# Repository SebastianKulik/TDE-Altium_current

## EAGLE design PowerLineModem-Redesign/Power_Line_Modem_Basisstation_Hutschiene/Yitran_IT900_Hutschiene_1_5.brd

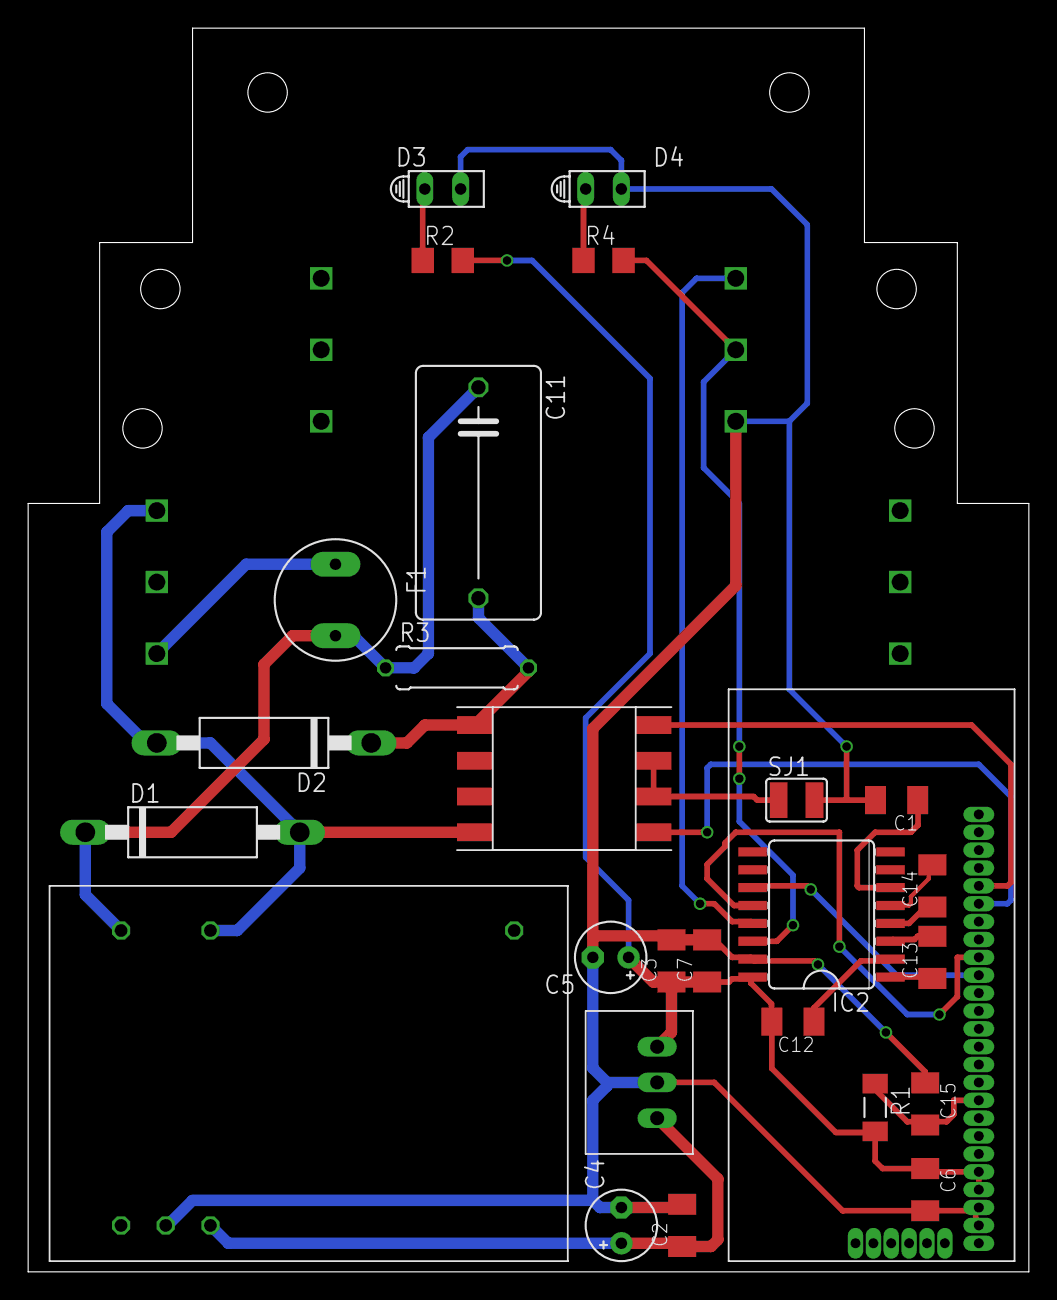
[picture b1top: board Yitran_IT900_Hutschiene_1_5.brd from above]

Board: 2 copper layers, 71.1 x 88.4 mm, 28 parts (0 on the bottom side), 23 nets.

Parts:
C1, C2, C3, C6, C7, C12, C13, C14, C15: 100n; C1206K
C4, C5: 4µ7; E2,5-5
C11: 470n; C150-091X182
D1: P6KE418C; CB417-15
D2: P6KE6V8C; CB417-15
D3: Power_3,3V rot; HLMP6
D4: TxD gruen; HLMP6
F1: 1A; TR5
IC2: MAX3232CWE; SO16L
R1: 100k; M1406
R2, R4: 330R; R1206
R3: 470k; 0309/10
SJ1: SJW
U$1: RECOM_783_3; RECOM785X
U$2: LDG-A-12
U$3: MODEMSTECKER; MODEM_FUSS
U$9: RECOM_RAC04_12SA; RAC04_12SA
U$10: PLC_UEBERTRAGER_V2; PLC-UEBERTRAGER_V2

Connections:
3V3: C3.1, C5.+, C6.1, C7.1, C12.2, IC2.16, R1.2, R2.2, U$1.VOUT, U$3.P$4, U$3.P$5
GND: C1.2, C2.2, C3.2, C4.-, C5.-, C6.2, C7.2, C15.1, D3.K, D4.K, IC2.15, SJ1.2, U$1.GND, U$2.P$10, U$3.P$2, U$3.P$3, U$9.GND
L: C11.1, D1.C, F1.2, R3.1, U$9.L
N: D1.A, D2.A, U$2.P$3, U$9.N, U$10.8N
unnamed: F1.1, U$2.P$1
unnamed: C11.2, D2.C, R3.2, U$10.L5
unnamed: C2.1, C4.+, U$1.VIN, U$9.+VO
unnamed: D3.A, R2.1
unnamed: U$3.P$21, U$10.1LINE1
unnamed: U$3.P$20, U$10.4LINE2
unnamed: C13.1, IC2.1
unnamed: C13.2, IC2.3
unnamed: C14.1, IC2.4
unnamed: C14.2, IC2.5
unnamed: C12.1, IC2.2
unnamed: C1.1, IC2.6
unnamed: D4.A, R4.1
unnamed: SJ1.1, U$10.2, U$10.3
unnamed: IC2.11, U$3.P$16
unnamed: IC2.12, U$3.P$17
unnamed: C15.2, R1.1, U$3.P$9
RXD: IC2.13, U$2.P$12
TXD: IC2.14, R4.2, U$2.P$11
